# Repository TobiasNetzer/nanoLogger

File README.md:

# Block Diagram

Here is a simplified block diagram of the data logger. To measure the current of a device, the data logger is simply connected in series between the voltage source and the DUT/load.

The current flow creates a small voltage drop across the selected shunt resistor, which is amplified by a factor of 100. The output voltage is then measured by the microcontroller's internal ADC.
A change of the current range is also observed by the microcontroller, to correctly convert the measured current.

An external trigger signal can optionally be connected. This allows to start the measurement on a rising or falling edge. Perfect to always have the same starting point of a measurement, for example when the DUT enters active mode.

Status LEDs provide the user with information about the device's current state/mode, for example: logger in standby mode, or data recording in progress.

The captured data is buffered internally in the microcontroller and then transferred to a PC via an isolated USB 2.0 interface.

# Hardware

I've written a very detailed explanation as part of the project documentation. You can read more about it [here](docs/Technikerarbeit_Tobias_Netzer.pdf) if you are interested in the design aspects and my thoughts behind them. This is also where you can find all the schematics and technical drawings. The documentation was however written in German.

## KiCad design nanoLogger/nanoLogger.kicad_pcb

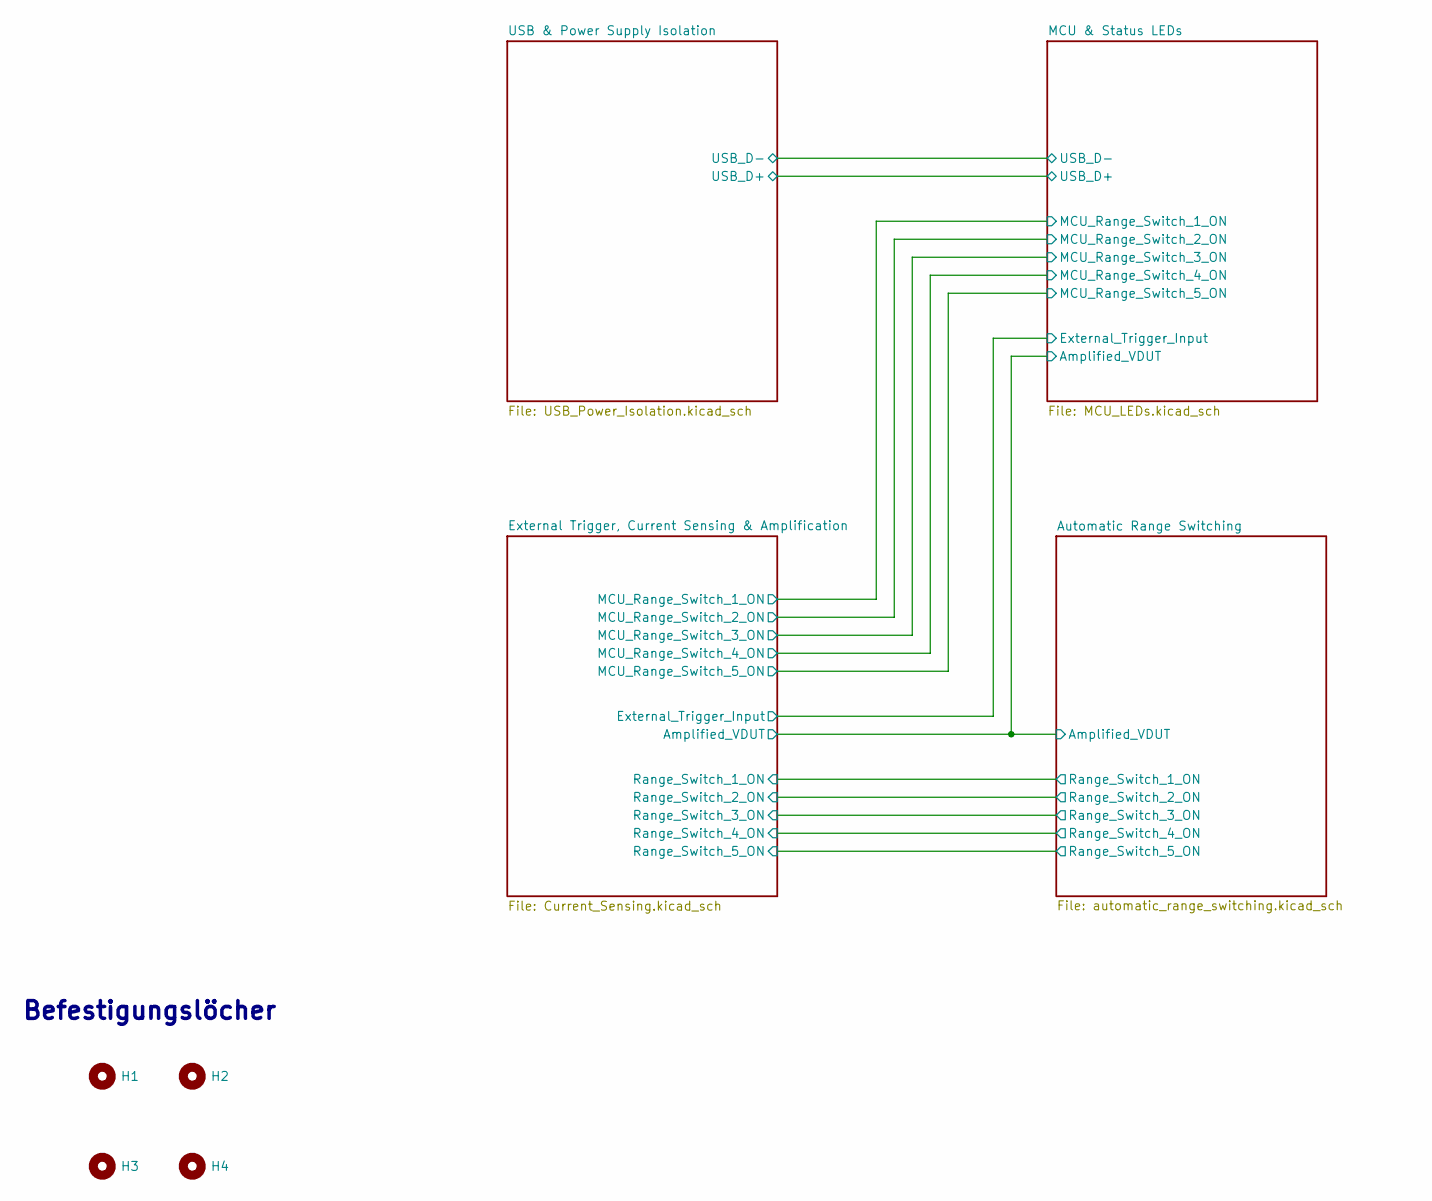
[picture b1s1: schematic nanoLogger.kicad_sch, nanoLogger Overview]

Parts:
H1, H2, H3, H4: MountingHole_M3

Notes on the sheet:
Befestigungslöcher

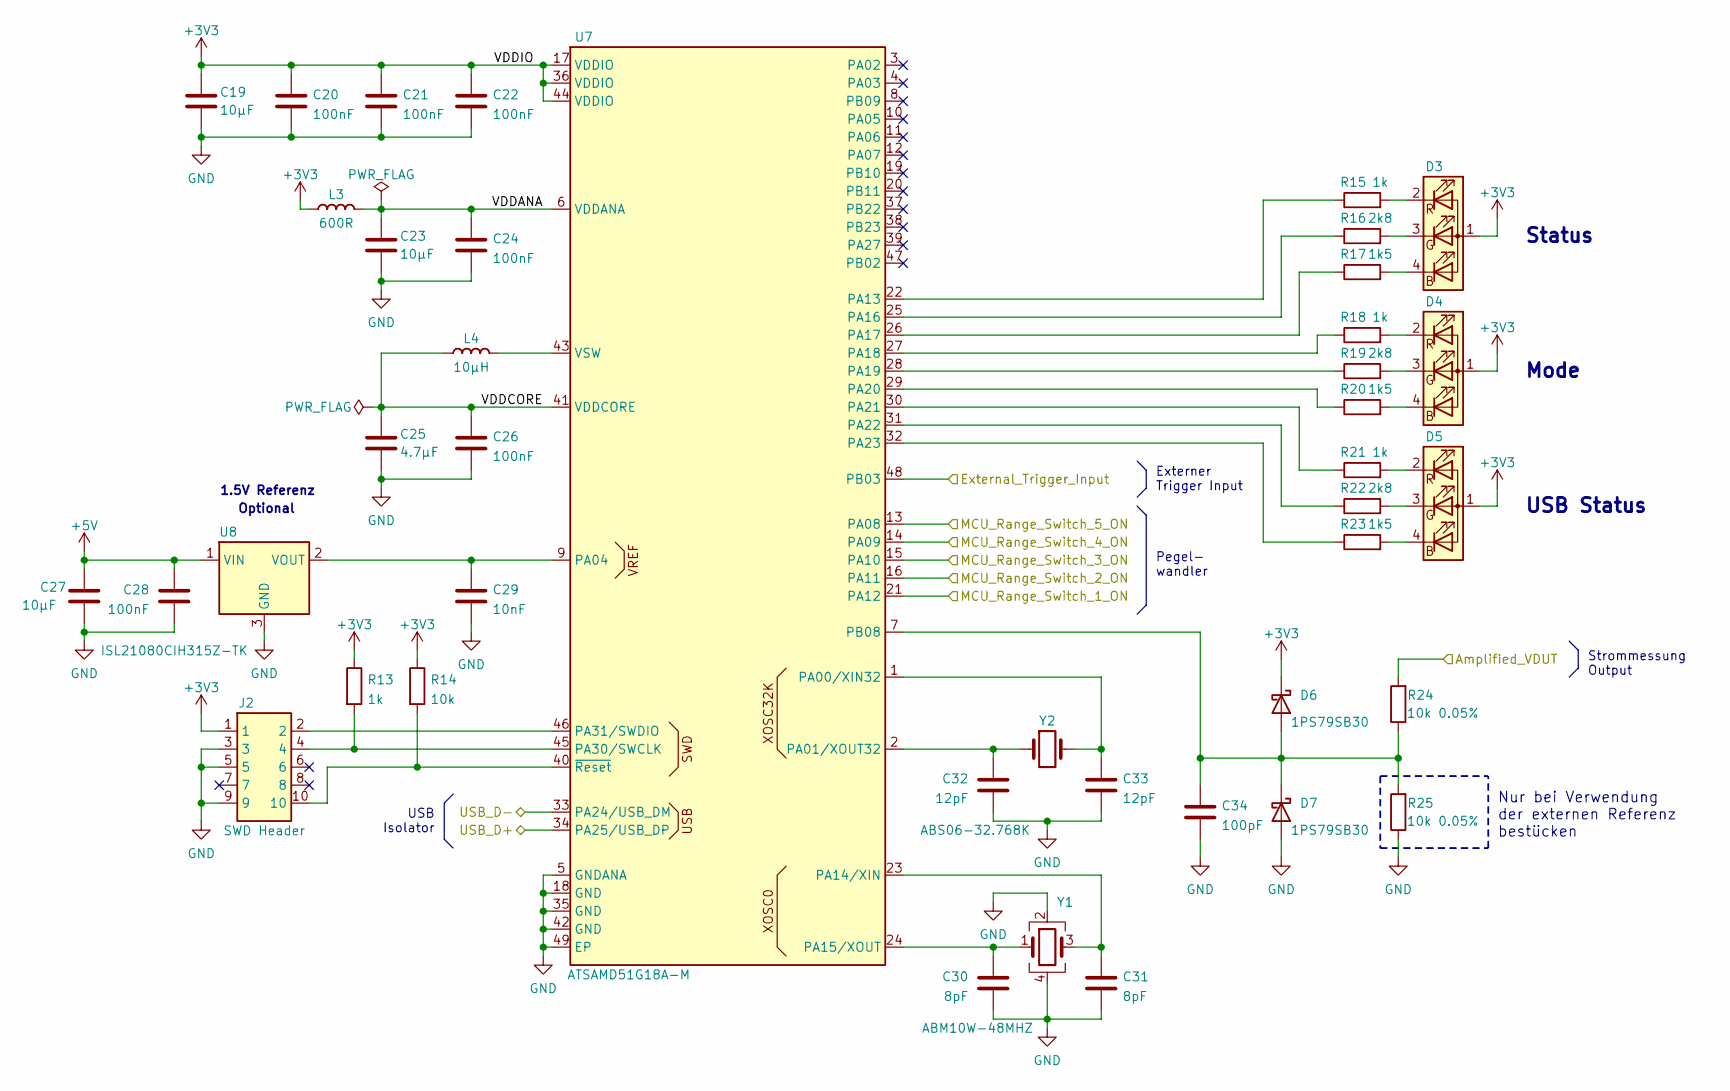
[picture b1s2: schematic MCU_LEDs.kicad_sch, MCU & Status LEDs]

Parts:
C19, C23, C27: 10µF; Capacitor_0603
C20, C21, C22, C24, C26, C28: 100nF; Capacitor_0402
C25: 4.7µF; Capacitor_0603
C29: 10nF; Capacitor_0402
C30, C31: 8pF; Capacitor_0402
C32, C33: 12pF; Capacitor_0402
C34: 100pF; Capacitor_0402
D3, D4, D5: Wuerth_150044M155260; LED_0404
D6, D7: 1PS79SB30; SOD523
J2: SWD Header; SAMTEC_FTSH-105-XX-X-DV
L3: 600R; Inductor_0402
L4: 10µH; Inductor_0603
R13, R15, R18, R21: 1k; Resistor_0402
R14: 10k; Resistor_0402
R16, R19, R22: 2k8; Resistor_0402
R17, R20, R23: 1k5; Resistor_0402
R24, R25: 10k 0.05%; Resistor_0402
U7: ATSAMD51G18A-M; VQFN-48
U8: ISL21080CIH315Z-TK; SOT-23
Y1: ABM10W-48MHZ; Abracon_ABM10_2.5x2.0mm
Y2: ABS06-32.768K; Abracon_ABS06

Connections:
+3V3: C19.2, C20.1, C21.1, C22.1, D3.1 (A), D4.1 (A), D5.1 (A), D6.1 (K), J2.1, L3.1, R13.1, R14.1, U7.17 (VDDIO), U7.36 (VDDIO), U7.44 (VDDIO); also elsewhere on the board
+5V: C27.2, C28.1, U8.1 (VIN); also elsewhere on the board
/Automatic Range Switching/Amplified_VDUT: R24.2; also elsewhere on the board
/External Trigger, Current Sensing & Amplification/External_Trigger_Input: U7.48 (PB03); also elsewhere on the board
/External Trigger, Current Sensing & Amplification/MCU_Range_Switch_1_ON: U7.21 (PA12); also elsewhere on the board
/External Trigger, Current Sensing & Amplification/MCU_Range_Switch_2_ON: U7.16 (PA11); also elsewhere on the board
/External Trigger, Current Sensing & Amplification/MCU_Range_Switch_3_ON: U7.15 (PA10); also elsewhere on the board
/External Trigger, Current Sensing & Amplification/MCU_Range_Switch_4_ON: U7.14 (PA09); also elsewhere on the board
/External Trigger, Current Sensing & Amplification/MCU_Range_Switch_5_ON: U7.13 (PA08); also elsewhere on the board
/MCU & Status LEDs/USB_D+: U7.34 (PA25/USB_DP); also elsewhere on the board
/MCU & Status LEDs/USB_D-: U7.33 (PA24/USB_DM); also elsewhere on the board
/MCU & Status LEDs/VDDANA: C23.2, C24.1, L3.2, U7.6 (VDDANA)
/MCU & Status LEDs/VDDCORE: C25.2, C26.1, L4.1, U7.41 (VDDCORE)
GND: C19.1, C20.2, C21.2, C22.2, C23.1, C24.2, C25.1, C26.2, C27.1, C28.2, C29.2, C30.2, C31.2, C32.2, C33.2, C34.2, D7.2 (A), J2.3, J2.5, J2.9, R25.1, U7.5 (GNDANA), U7.18 (GND), U7.35 (GND), U7.42 (GND), U7.49 (EP), U8.3 (GND), Y1.2, Y1.4; also elsewhere on the board
unnamed: C29.1, U7.9 (PA04), U8.2 (VOUT)
unnamed: C30.1, U7.24 (PA15/XOUT), Y1.1
unnamed: C31.1, U7.23 (PA14/XIN), Y1.3
unnamed: C32.1, U7.2 (PA01/XOUT32), Y2.1
unnamed: C33.1, U7.1 (PA00/XIN32), Y2.2
unnamed: C34.1, D6.2 (A), D7.1 (K), R24.1, R25.2, U7.7 (PB08)
unnamed: D3.2 (RK), R15.2
unnamed: D3.3 (GK), R16.2
unnamed: D3.4 (BK), R17.2
unnamed: D4.2 (RK), R18.2
unnamed: D4.3 (GK), R19.2
unnamed: D4.4 (BK), R20.2
unnamed: D5.2 (RK), R21.2
unnamed: D5.3 (GK), R22.2
unnamed: D5.4 (BK), R23.2
unnamed: J2.2, U7.46 (PA31/SWDIO)
unnamed: J2.4, R13.2, U7.45 (PA30/SWCLK)
unnamed: J2.10, R14.2, U7.40 (~Reset)
unnamed: L4.2, U7.43 (VSW)
unnamed: R15.1, U7.22 (PA13)
unnamed: R16.1, U7.25 (PA16)
unnamed: R17.1, U7.26 (PA17)
unnamed: R18.1, U7.27 (PA18)
unnamed: R19.1, U7.28 (PA19)
unnamed: R20.1, U7.29 (PA20)
unnamed: R21.1, U7.30 (PA21)
unnamed: R22.1, U7.31 (PA22)
unnamed: R23.1, U7.32 (PA23)

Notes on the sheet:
Optional
Status
Strommessung Output
Externer Trigger Input
USB Isolator
Pegel- wandler
Mode
Nur bei Verwendung der externen Referenz bestücken
USB Status
1.5V Referenz

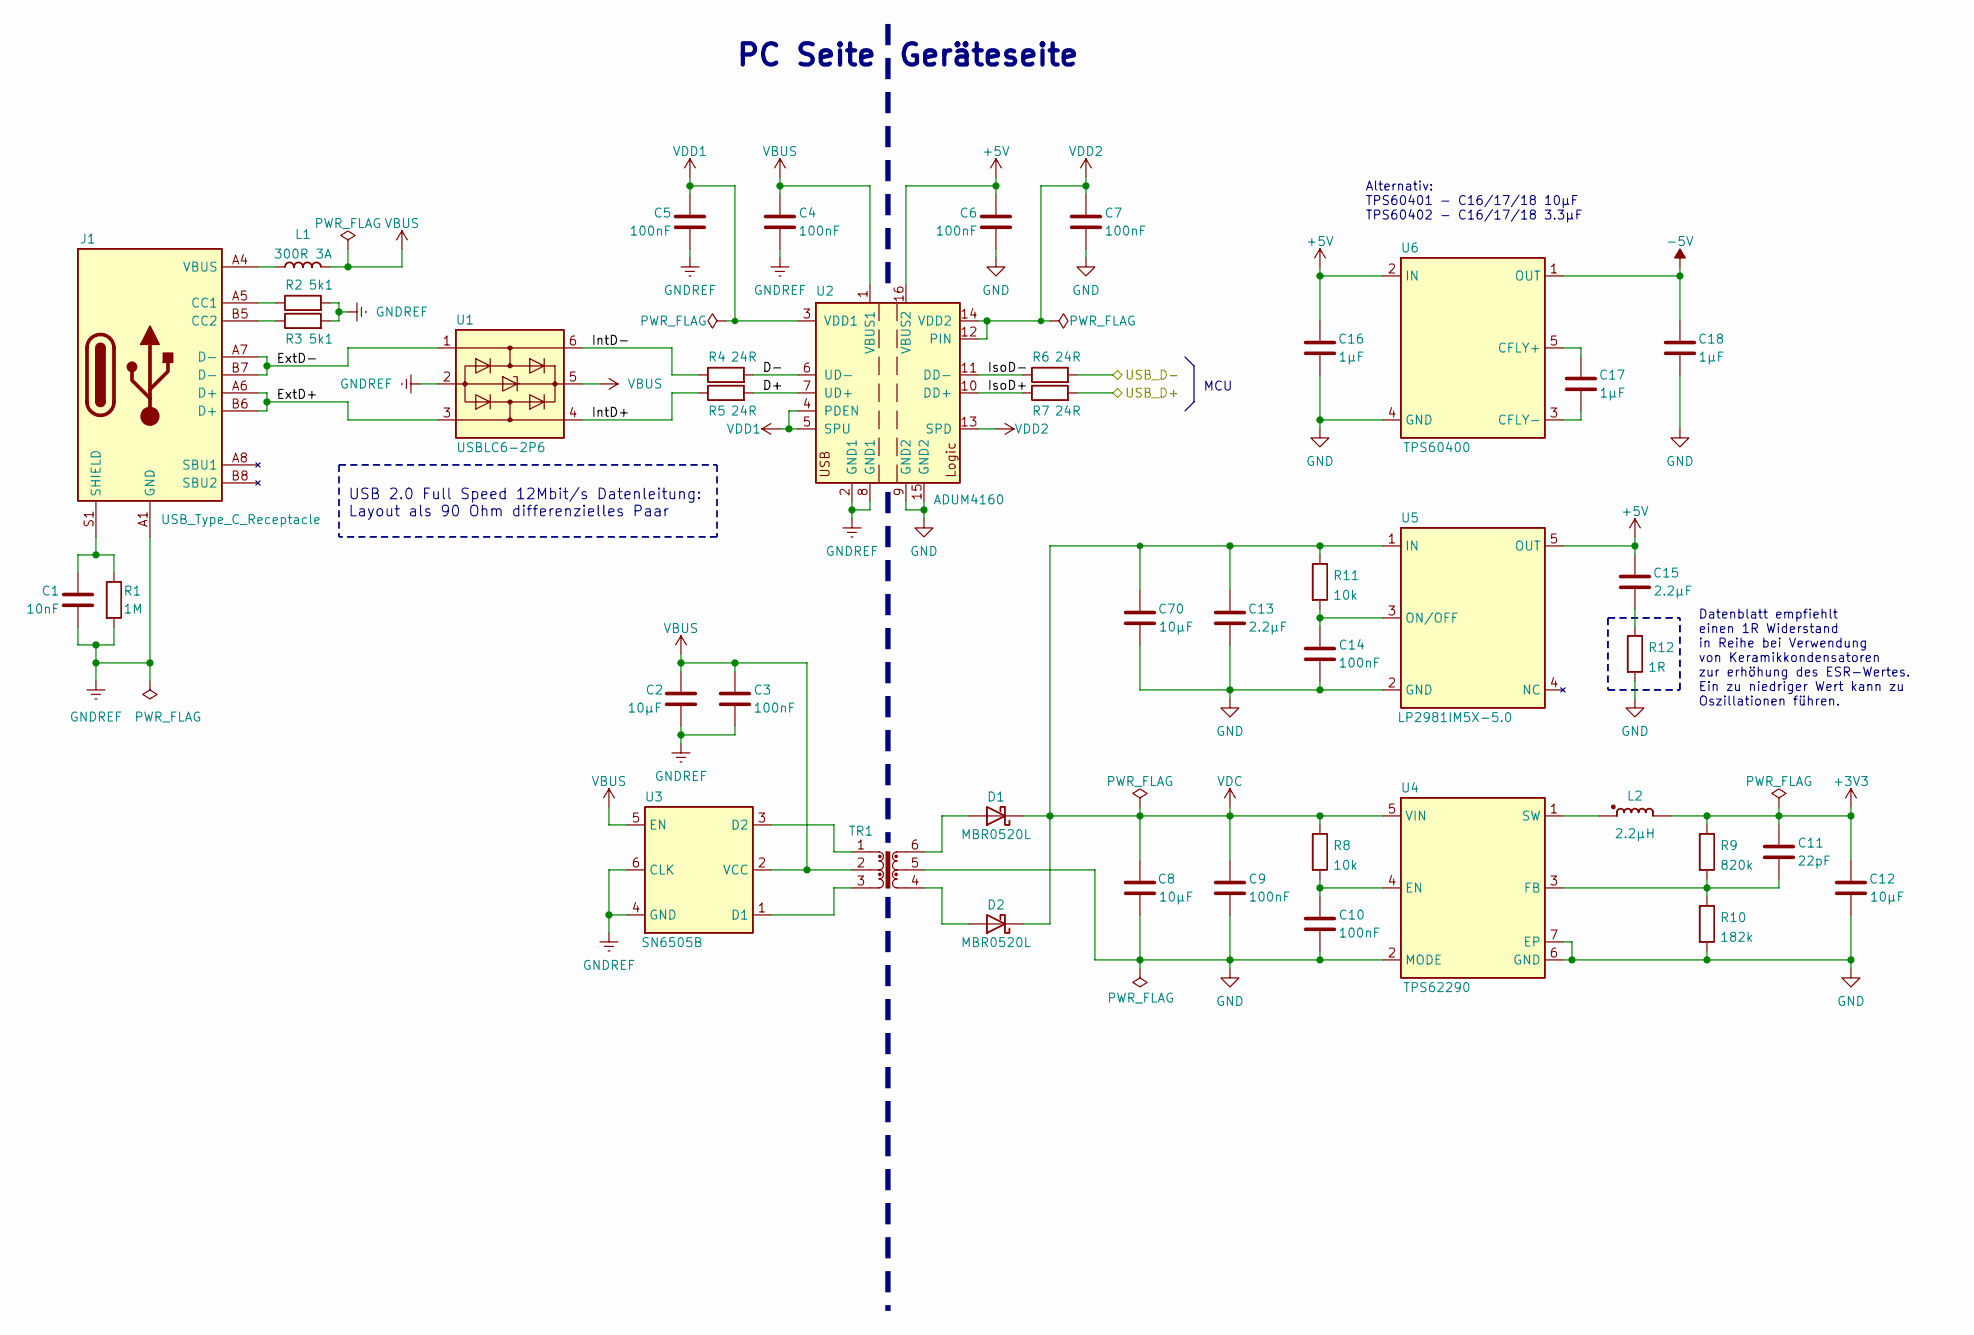
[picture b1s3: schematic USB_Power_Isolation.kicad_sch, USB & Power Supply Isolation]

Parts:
C1: 10nF; Capacitor_1206
C2, C8, C12: 10µF; Capacitor_0603
C3, C4, C5, C6, C7, C9, C10, C14: 100nF; Capacitor_0402
C11: 22pF; Capacitor_0402
C13, C15: 2.2µF; Capacitor_0603
C16, C17, C18: 1µF; Capacitor_0603
C70: 10µF; Capacitor_1206
D1, D2: MBR0520L; SOD-123
J1: USB_Type_C_Receptacle; USB_C_Receptacle_HRO_TYPE-C-31-M-12
L1: 300R 3A; Inductor_0805
L2: 2.2µH; LPS3015
R1: 1M; Resistor_1206
R2, R3: 5k1; Resistor_0402
R4, R5, R6, R7: 24R; Resistor_0402
R8, R11: 10k; Resistor_0402
R9: 820k; Resistor_0402
R10: 182k; Resistor_0402
R12: 1R; Resistor_0402
TR1: Wuerth_750315371; Transformer_Wuerth_750315371
U1: USBLC6-2P6; SOT-666
U2: ADUM4160; SOIC-16W
U3: SN6505B; SOT-23-6
U4: TPS62290; SON-6
U5: LP2981IM5X-5.0; SOT-23-5
U6: TPS60400; SOT-23-5

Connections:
+3V3: C11.1, C12.2, L2.2, R9.1; also elsewhere on the board
+5V: C6.1, C15.2, C16.2, U2.16 (VBUS2), U5.5 (OUT), U6.2 (IN); also elsewhere on the board
-5V: C18.2, U6.1 (OUT); also elsewhere on the board
/MCU & Status LEDs/USB_D+: R7.2; also elsewhere on the board
/MCU & Status LEDs/USB_D-: R6.2; also elsewhere on the board
/USB & Power Supply Isolation/D+: R5.2, U2.7 (UD+)
/USB & Power Supply Isolation/D-: R4.2, U2.6 (UD-)
/USB & Power Supply Isolation/ExtD+: J1.A6 (D+), J1.B6 (D+), U1.3 (I/O2)
/USB & Power Supply Isolation/ExtD-: J1.A7 (D-), J1.B7 (D-), U1.1 (I/O1)
/USB & Power Supply Isolation/IntD+: R5.1, U1.4 (I/O2)
/USB & Power Supply Isolation/IntD-: R4.1, U1.6 (I/O1)
/USB & Power Supply Isolation/IsoD+: R7.1, U2.10 (DD+)
/USB & Power Supply Isolation/IsoD-: R6.1, U2.11 (DD-)
GND: C6.2, C7.2, C8.1, C9.2, C10.2, C12.1, C13.1, C14.2, C16.1, C18.1, C70.2, R10.2, R12.2, TR1.5, U2.9 (GND2), U2.15 (GND2), U4.2 (MODE), U4.6 (GND), U4.7 (EP), U5.2 (GND), U6.4 (GND); also elsewhere on the board
GNDREF: C1.2, C2.1, C3.2, C4.2, C5.2, J1.A1 (GND), J1.A12 (GND), J1.B1 (GND), J1.B12 (GND), R1.2, R2.2, R3.2, U1.2 (GND), U2.2 (GND1), U2.8 (GND1), U3.4 (GND), U3.6 (CLK)
unnamed: C1.1, J1.S1 (SHIELD), R1.1
unnamed: C10.1, R8.2, U4.4 (EN)
unnamed: C11.2, R9.2, R10.1, U4.3 (FB)
unnamed: C14.1, R11.2, U5.3 (ON/OFF)
unnamed: C15.1, R12.1
unnamed: C17.1, U6.3 (CFLY-)
unnamed: C17.2, U6.5 (CFLY+)
unnamed: D1.2 (A), TR1.6
unnamed: D2.2 (A), TR1.4
unnamed: J1.A4 (VBUS), J1.A9 (VBUS), J1.B4 (VBUS), J1.B9 (VBUS), L1.1
unnamed: J1.A5 (CC1), R2.1
unnamed: J1.B5 (CC2), R3.1
unnamed: L2.1, U4.1 (SW)
unnamed: TR1.1, U3.3 (D2)
unnamed: TR1.3, U3.1 (D1)
VBUS: C2.2, C3.1, C4.1, L1.2, TR1.2, U1.5 (VBUS), U2.1 (VBUS1), U3.2 (VCC), U3.5 (EN)
VDC: C8.2, C9.1, C13.2, C70.1, D1.1 (K), D2.1 (K), R8.1, R11.1, U4.5 (VIN), U5.1 (IN)
VDD1: C5.1, U2.3 (VDD1), U2.4 (PDEN), U2.5 (SPU)
VDD2: C7.1, U2.12 (PIN), U2.13 (SPD), U2.14 (VDD2)

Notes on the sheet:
Geräteseite
MCU
PC Seite
Alternativ: TPS60401 - C16/17/18 10µF TPS60402 - C16/17/18 3.3µF
USB 2.0 Full Speed 12Mbit/s Datenleitung: Layout als 90 Ohm differenzielles Paar
Datenblatt empfiehlt einen 1R Widerstand in Reihe bei Verwendung von Keramikkondensatoren zur erhöhung des ESR-Wertes. Ein zu niedriger Wert kann zu Oszillationen führen.

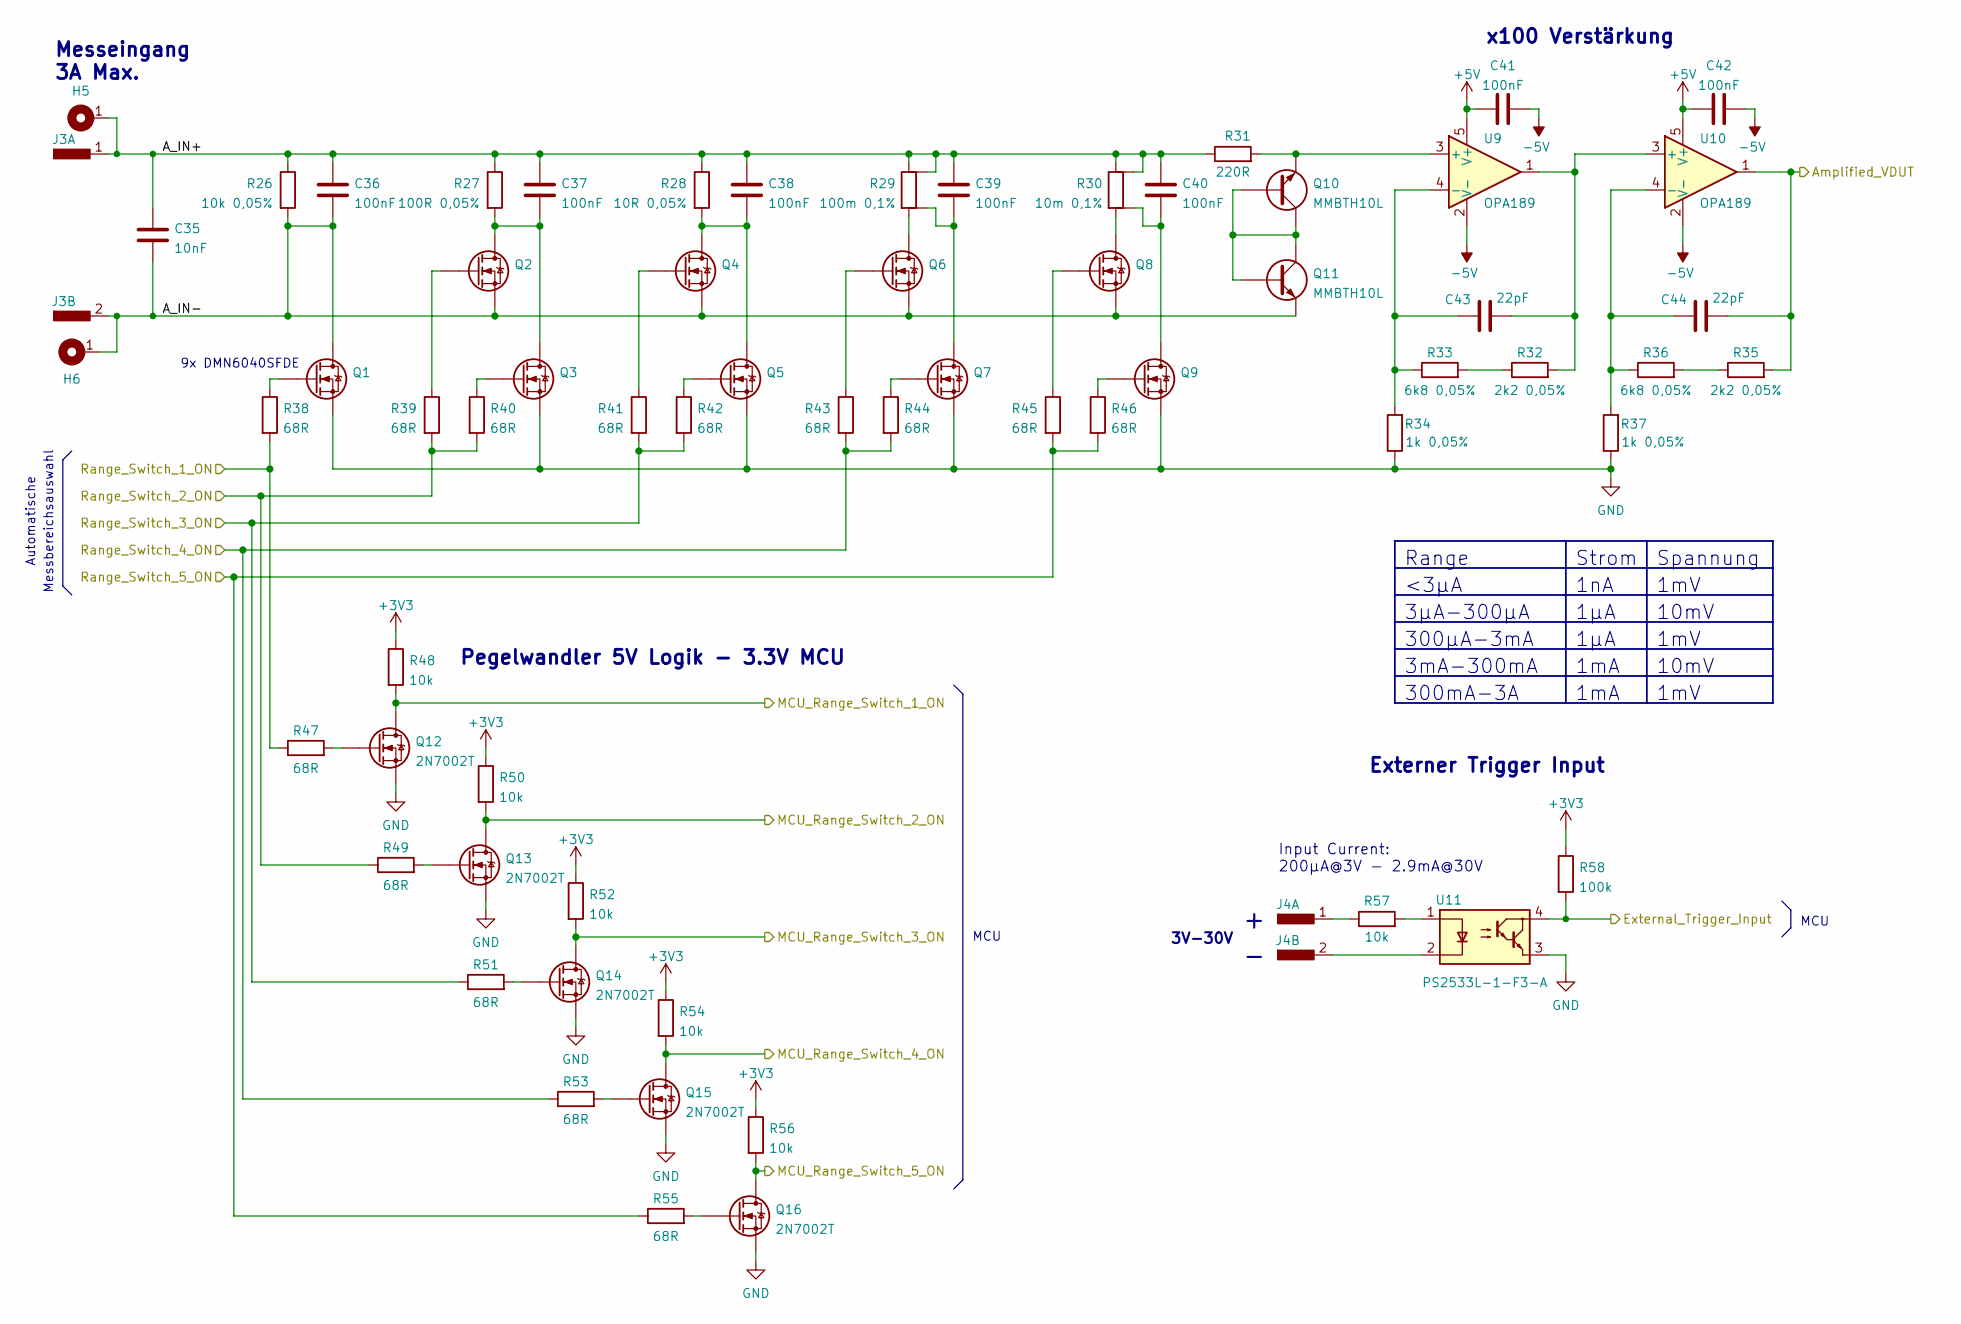
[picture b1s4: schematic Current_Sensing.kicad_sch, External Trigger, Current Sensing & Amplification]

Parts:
C35: 10nF; Capacitor_1206
C36, C37, C38, C39, C40, C41, C42: 100nF; Capacitor_0402
C43, C44: 22pF; Capacitor_0402
H5, H6: MountingHole_M2
J3, J4: PinHeader_2_54mm_2pol_smd; PinHeader_Male_2_54mm_2pin_smd
Q1, Q2, Q3, Q4, Q5, Q6, Q7, Q8, Q9: DMN6040SFDE; UDFN2020-6_Type-E
Q10, Q11: MMBTH10L; SOT-23
Q12, Q13, Q14, Q15, Q16: 2N7002T; SOT-523
R26: 10k 0,05%; Resistor_0805
R27: 100R 0,05%; Resistor_0805
R28: 10R 0,05%; Resistor_0805
R29: 100m 0,1%; Resistor_CSM2512
R30: 10m 0,1%; Resistor_CSM2512
R31: 220R; Resistor_0805
R32, R35: 2k2 0,05%; Resistor_0402
R33, R36: 6k8 0,05%; Resistor_0402
R34, R37: 1k 0,05%; Resistor_0402
R38, R39, R40, R41, R42, R43, R44, R45, R46, R47, R49, R51, R53, R55: 68R; Resistor_0402
R48, R50, R52, R54, R56: 10k; Resistor_0402
R57: 10k; Resistor_0805
R58: 100k; Resistor_0402
U9, U10: OPA189; SOT-23-5
U11: PS2533L-1-F3-A; DIP-4

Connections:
+3V3: R48.1, R50.1, R52.1, R54.1, R56.1, R58.1; also elsewhere on the board
+5V: C41.1, C42.1, U9.5 (V+), U10.5 (V+); also elsewhere on the board
-5V: C41.2, C42.2, U9.2 (V-), U10.2 (V-); also elsewhere on the board
/Automatic Range Switching/Amplified_VDUT: C44.2, R35.2, U10.1; also elsewhere on the board
/Automatic Range Switching/Range_Switch_1_ON: R38.2, R47.1; also elsewhere on the board
/Automatic Range Switching/Range_Switch_2_ON: R39.2, R40.2, R49.1; also elsewhere on the board
/Automatic Range Switching/Range_Switch_3_ON: R41.2, R42.2, R51.1; also elsewhere on the board
/Automatic Range Switching/Range_Switch_4_ON: R43.2, R44.2, R53.1; also elsewhere on the board
/Automatic Range Switching/Range_Switch_5_ON: R45.2, R46.2, R55.1; also elsewhere on the board
/External Trigger, Current Sensing & Amplification/A_IN+: C35.1, C36.1, C37.1, C38.1, C39.1, C40.1, H5.1, J3.1, R26.1, R27.1, R28.1, R29.1, R29.2, R30.1, R30.2, R31.1
/External Trigger, Current Sensing & Amplification/A_IN-: C35.2, C36.2, H6.1, J3.2, Q1.1 (D), Q1.2 (D), Q1.5 (D), Q1.6 (D), Q1.7 (D), Q2.4 (S), Q2.8 (S), Q4.4 (S), Q4.8 (S), Q6.4 (S), Q6.8 (S), Q8.4 (S), Q8.8 (S), Q11.2 (E), R26.2
/External Trigger, Current Sensing & Amplification/External_Trigger_Input: R58.2, U11.4; also elsewhere on the board
/External Trigger, Current Sensing & Amplification/MCU_Range_Switch_1_ON: Q12.3 (D), R48.2; also elsewhere on the board
/External Trigger, Current Sensing & Amplification/MCU_Range_Switch_2_ON: Q13.3 (D), R50.2; also elsewhere on the board
/External Trigger, Current Sensing & Amplification/MCU_Range_Switch_3_ON: Q14.3 (D), R52.2; also elsewhere on the board
/External Trigger, Current Sensing & Amplification/MCU_Range_Switch_4_ON: Q15.3 (D), R54.2; also elsewhere on the board
/External Trigger, Current Sensing & Amplification/MCU_Range_Switch_5_ON: Q16.3 (D), R56.2; also elsewhere on the board
GND: Q1.4 (S), Q1.8 (S), Q3.4 (S), Q3.8 (S), Q5.4 (S), Q5.8 (S), Q7.4 (S), Q7.8 (S), Q9.4 (S), Q9.8 (S), Q12.2 (D), Q13.2 (D), Q14.2 (D), Q15.2 (D), Q16.2 (D), R34.1, R37.1, U11.3; also elsewhere on the board
unnamed: C37.2, Q2.1 (D), Q2.2 (D), Q2.5 (D), Q2.6 (D), Q2.7 (D), Q3.1 (D), Q3.2 (D), Q3.5 (D), Q3.6 (D), Q3.7 (D), R27.2
unnamed: C38.2, Q4.1 (D), Q4.2 (D), Q4.5 (D), Q4.6 (D), Q4.7 (D), Q5.1 (D), Q5.2 (D), Q5.5 (D), Q5.6 (D), Q5.7 (D), R28.2
unnamed: C39.2, Q7.1 (D), Q7.2 (D), Q7.5 (D), Q7.6 (D), Q7.7 (D), R29.3
unnamed: C40.2, Q9.1 (D), Q9.2 (D), Q9.5 (D), Q9.6 (D), Q9.7 (D), R30.3
unnamed: C43.1, R33.1, R34.2, U9.4 (-)
unnamed: C43.2, R32.2, U9.1, U10.3 (+)
unnamed: C44.1, R36.1, R37.2, U10.4 (-)
unnamed: J4.1, R57.1
unnamed: J4.2, U11.2
unnamed: Q1.3 (G), R38.1
unnamed: Q2.3 (G), R39.1
unnamed: Q3.3 (G), R40.1
unnamed: Q4.3 (G), R41.1
unnamed: Q5.3 (G), R42.1
unnamed: Q6.1 (D), Q6.2 (D), Q6.5 (D), Q6.6 (D), Q6.7 (D), R29.4
unnamed: Q6.3 (G), R43.1
unnamed: Q7.3 (G), R44.1
unnamed: Q8.1 (D), Q8.2 (D), Q8.5 (D), Q8.6 (D), Q8.7 (D), R30.4
unnamed: Q8.3 (G), R45.1
unnamed: Q9.3 (G), R46.1
unnamed: Q10.1 (B), Q10.3 (C), Q11.1 (B), Q11.3 (C)
unnamed: Q10.2 (E), R31.2, U9.3 (+)
unnamed: Q12.1 (G), R47.2
unnamed: Q13.1 (G), R49.2
unnamed: Q14.1 (G), R51.2
unnamed: Q15.1 (G), R53.2
unnamed: Q16.1 (G), R55.2
unnamed: R32.1, R33.2
unnamed: R35.1, R36.2
unnamed: R57.2, U11.1

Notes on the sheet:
Input Current: 200µA@3V - 2.9mA@30V
10mV
1mA
Pegelwandler 5V Logik - 3.3V MCU
300µA-3mA
Externer Trigger Input
Range
1mV
Messeingang 3A Max.
MCU
Spannung
Automatische
3V-30V
300mA-3A
9x DMN6040SFDE
1µA
3mA-300mA
Messbereichsauswahl
x100 Verstärkung
3µA-300µA
Strom
1nA
<3µA

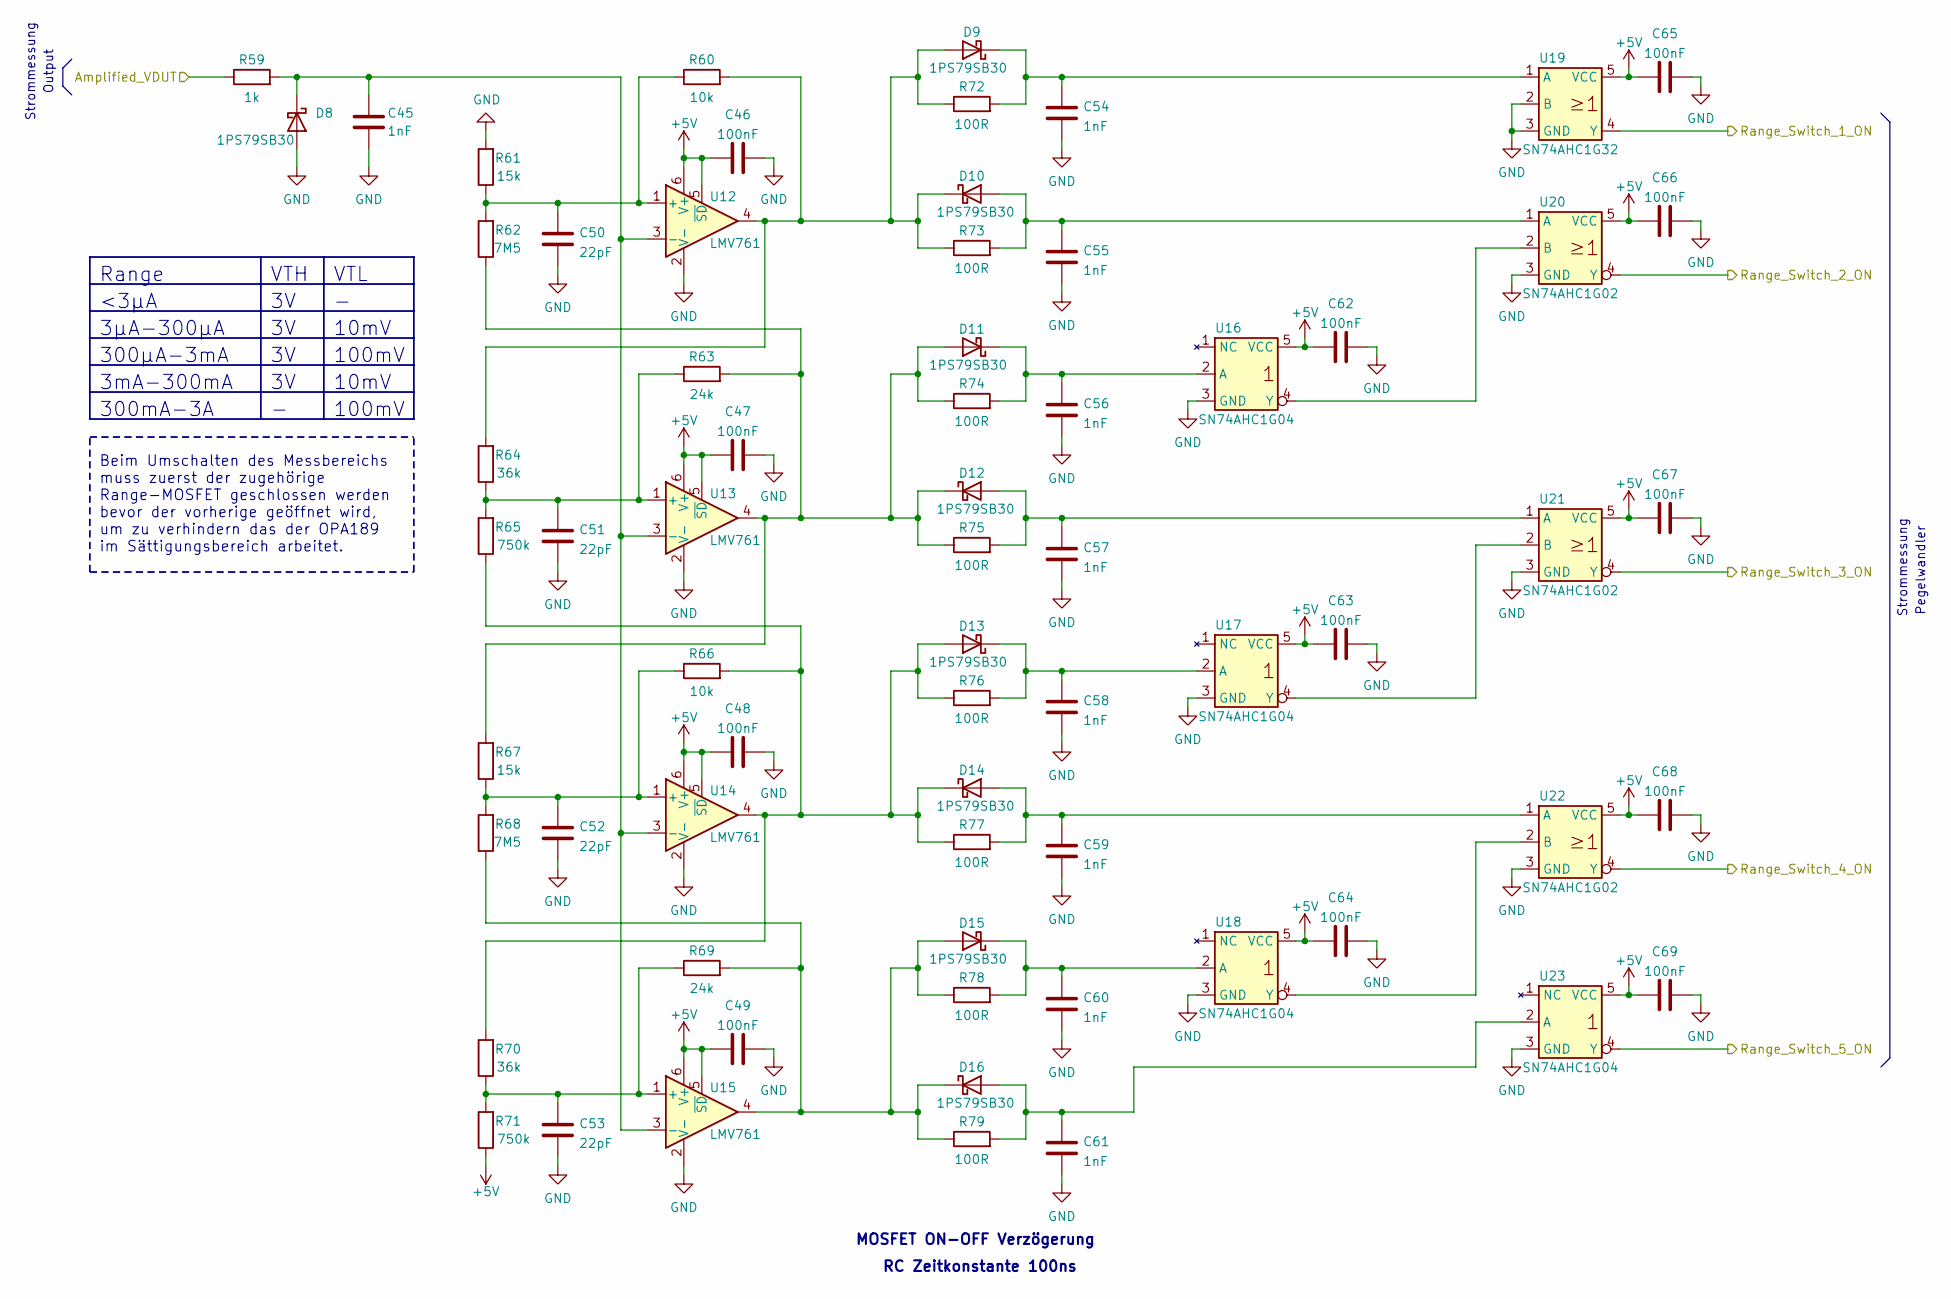
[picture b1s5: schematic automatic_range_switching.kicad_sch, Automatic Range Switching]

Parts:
C45, C54, C55, C56, C57, C58, C59, C60, C61: 1nF; Capacitor_0402
C46, C47, C48, C49, C62, C63, C64, C65, C66, C67, C68, C69: 100nF; Capacitor_0402
C50, C51, C52, C53: 22pF; Capacitor_0402
D8, D9, D10, D11, D12, D13, D14, D15, D16: 1PS79SB30; SOD523
R59: 1k; Resistor_0402
R60, R66: 10k; Resistor_0402
R61, R67: 15k; Resistor_0402
R62, R68: 7M5; Resistor_0402
R63, R69: 24k; Resistor_0402
R64, R70: 36k; Resistor_0402
R65, R71: 750k; Resistor_0402
R72, R73, R74, R75, R76, R77, R78, R79: 100R; Resistor_0402
U12, U13, U14, U15: LMV761; SOT-23-6
U16, U17, U18, U23: SN74AHC1G04; SOT-553
U19: SN74AHC1G32; SOT-553
U20, U21, U22: SN74AHC1G02; SOT-553

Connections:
+5V: C46.1, C47.1, C48.1, C49.1, C62.1, C63.1, C64.1, C65.1, C66.1, C67.1, C68.1, C69.1, R71.1, U12.5 (~SD), U12.6 (V+), U13.5 (~SD), U13.6 (V+), U14.5 (~SD), U14.6 (V+), U15.5 (~SD), U15.6 (V+), U16.5 (VCC), U17.5 (VCC), U18.5 (VCC), U19.5 (VCC), U20.5 (VCC), U21.5 (VCC), U22.5 (VCC), U23.5 (VCC); also elsewhere on the board
/Automatic Range Switching/Amplified_VDUT: R59.1; also elsewhere on the board
/Automatic Range Switching/Range_Switch_1_ON: U19.4 (Y); also elsewhere on the board
/Automatic Range Switching/Range_Switch_2_ON: U20.4 (Y); also elsewhere on the board
/Automatic Range Switching/Range_Switch_3_ON: U21.4 (Y); also elsewhere on the board
/Automatic Range Switching/Range_Switch_4_ON: U22.4 (Y); also elsewhere on the board
/Automatic Range Switching/Range_Switch_5_ON: U23.4 (Y); also elsewhere on the board
GND: C45.2, C46.2, C47.2, C48.2, C49.2, C50.2, C51.2, C52.2, C53.2, C54.2, C55.2, C56.2, C57.2, C58.2, C59.2, C60.2, C61.2, C62.2, C63.2, C64.2, C65.2, C66.2, C67.2, C68.2, C69.2, D8.2 (A), R61.2, U12.2 (V-), U13.2 (V-), U14.2 (V-), U15.2 (V-), U16.3 (GND), U17.3 (GND), U18.3 (GND), U19.2 (B), U19.3 (GND), U20.3 (GND), U21.3 (GND), U22.3 (GND), U23.3 (GND); also elsewhere on the board
unnamed: C45.1, D8.1 (K), R59.2, U12.3 (-), U13.3 (-), U14.3 (-), U15.3 (-)
unnamed: C50.1, R60.1, R61.1, R62.2, U12.1 (+)
unnamed: C51.1, R63.1, R64.1, R65.2, U13.1 (+)
unnamed: C52.1, R66.1, R67.1, R68.2, U14.1 (+)
unnamed: C53.1, R69.1, R70.1, R71.2, U15.1 (+)
unnamed: C54.1, D9.1 (K), R72.2, U19.1 (A)
unnamed: C55.1, D10.2 (A), R73.2, U20.1 (A)
unnamed: C56.1, D11.1 (K), R74.2, U16.2 (A)
unnamed: C57.1, D12.2 (A), R75.2, U21.1 (A)
unnamed: C58.1, D13.1 (K), R76.2, U17.2 (A)
unnamed: C59.1, D14.2 (A), R77.2, U22.1 (A)
unnamed: C60.1, D15.1 (K), R78.2, U18.2 (A)
unnamed: C61.1, D16.2 (A), R79.2, U23.2 (A)
unnamed: D9.2 (A), D10.1 (K), R60.2, R64.2, R72.1, R73.1, U12.4
unnamed: D11.2 (A), D12.1 (K), R62.1, R63.2, R67.2, R74.1, R75.1, U13.4
unnamed: D13.2 (A), D14.1 (K), R65.1, R66.2, R70.2, R76.1, R77.1, U14.4
unnamed: D15.2 (A), D16.1 (K), R68.1, R69.2, R78.1, R79.1, U15.4
unnamed: U16.4 (Y), U20.2 (B)
unnamed: U17.4 (Y), U21.2 (B)
unnamed: U18.4 (Y), U22.2 (B)

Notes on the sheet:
10mV
300µA-3mA
100mV
Beim Umschalten des Messbereichs muss zuerst der zugehörige Range-MOSFET geschlossen werden bevor der vorherige geöffnet wird, um zu verhindern das der OPA189 im Sättigungsbereich arbeitet.
Pegelwandler
3µA-300µA
300mA-3A
RC Zeitkonstante 100ns
3mA-300mA
MOSFET ON-OFF Verzögerung
Strommessung
Output
VTL
VTH
Range
<3µA
